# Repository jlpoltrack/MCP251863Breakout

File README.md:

# MCP251863Breakout

A CAN FD breakout: an MCP251863 (CAN FD controller with integrated transceiver) on SPI, with an
onboard 3.3 V regulator and 120 Ω termination. All connections are solder pads.

Designed in KiCad 10. See [SimpleCANBreakout](https://github.com/jlpoltrack/SimpleCANBreakout) for a classic-CAN
transceiver-only board.

## Features

- MCP251863 CAN FD controller + transceiver (SSOP-28), SPI interface, STBY on its own pad
- 4-pin crystal (Y1, 2016) for the controller clock
- AMS1117 3.3 V LDO for VDD/VIO; transceiver VCC from +5V
- 120 Ω termination resistor, always fitted
- Parts on the top side only

## Connections

All pads are 2.0 × 2.0 mm, labelled with their signal name.

| Pad  | Signal                              |
|------|-------------------------------------|
| CS   | SPI chip select (active low)        |
| SCK  | SPI clock                           |
| MOSI | SPI data in (SDI)                   |
| MISO | SPI data out (SDO)                  |
| INT  | interrupt (active low)              |
| INT0 | GPIO0 / TX interrupt (active low)   |
| INT1 | GPIO1 / RX interrupt (active low)   |
| CLKO | clock output                        |
| STBY | transceiver standby (high = standby) |
| CANH | CAN bus high                        |
| CANL | CAN bus low                         |
| PWR  | +5V (two pads: bottom edge, and beside CANH) |
| GND  | GND (two pads: bottom edge, and beside CANL) |

SPI, interrupt and STBY pins are 3.3 V logic (VIO = 3.3 V). STBY has no pull-down on the board: drive it low (or tie it
to GND) for normal operation; the transceiver goes to standby when it is high. INT0 (GPIO0) can drive it as XSTBY.

## Termination

R1 (120 Ω) is permanently connected across CANH/CANL, so the board is meant to sit at an end of the bus. Leave R1
unpopulated if the board is used mid-bus.

## Bill of materials

| Ref                  | Value           | Package    | LCSC    |
|----------------------|-----------------|------------|---------|
| U1                   | MCP251863T-H/SS | SSOP-28    |         |
| U2                   | AMS1117-3.3     | SOT-223    | C6186   |
| Y1                   | crystal         | 2016 4-pin |         |
| C1, C4, C10, C12     | 10 µF 25 V X5R  | 0603       | C96446  |
| C2, C3, C5, C6, C7   | 100 nF 50 V X7R | 0603       | C14663  |
| C8, C9               | 10 pF 50 V C0G  | 0603       | C1634   |
| R1                   | 120 Ω 1 %       | 0603       | C22787  |

All LCSC numbers above are JLC basic parts. U1 and Y1 have none set.

## Files

- `MCP251863Breakout.kicad_sch` / `.kicad_pcb` / `.kicad_pro` — KiCad project
- `MCP251863Breakout.pdf` — schematic
- `production/` — fabrication outputs generated with the [Fabrication Toolkit](https://github.com/bennymeg/Fabrication-Toolkit) plugin: Gerbers and drill files (`MCP251863Breakout.zip`), BOM, and pick-and-place positions, ready for JLCPCB

## License

[MIT](LICENSE)

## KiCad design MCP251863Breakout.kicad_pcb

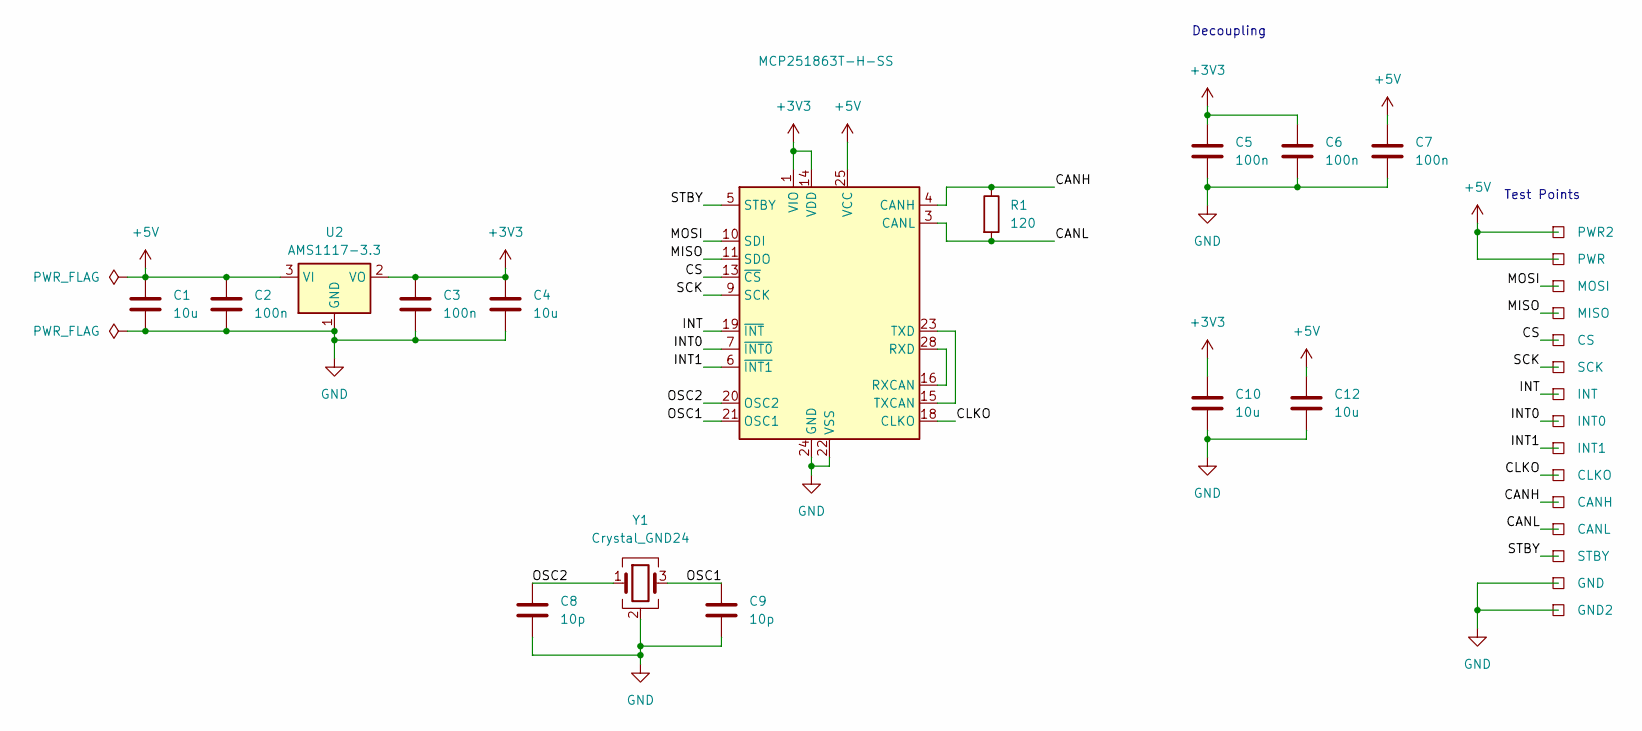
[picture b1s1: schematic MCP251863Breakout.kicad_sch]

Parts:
C1, C4, C10, C12: 10u; C_0603_1608Metric_Pad1.08x0.95mm_HandSolder; LCSC Part C96446
C2, C3, C5, C6, C7: 100n; C_0603_1608Metric_Pad1.08x0.95mm_HandSolder; LCSC Part C14663
C8, C9: 10p; C_0603_1608Metric_Pad1.08x0.95mm_HandSolder; LCSC Part C1634
CANH: TestPoint_Square; TestPoint_Pad_2.0x2.0mm
CANL: TestPoint_Square; TestPoint_Pad_2.0x2.0mm
CLKO: TestPoint_Square; TestPoint_Pad_2.0x2.0mm
CS: TestPoint_Square; TestPoint_Pad_2.0x2.0mm
GND, GND2: TestPoint_Square; TestPoint_Pad_2.0x2.0mm
INT, INT0, INT1: TestPoint_Square; TestPoint_Pad_2.0x2.0mm
MISO: TestPoint_Square; TestPoint_Pad_2.0x2.0mm
MOSI: TestPoint_Square; TestPoint_Pad_2.0x2.0mm
PWR, PWR2: TestPoint_Square; TestPoint_Pad_2.0x2.0mm
R1: 120; C_0603_1608Metric_Pad1.08x0.95mm_HandSolder; LCSC Part C22787
SCK: TestPoint_Square; TestPoint_Pad_2.0x2.0mm
STBY: TestPoint_Square; TestPoint_Pad_2.0x2.0mm
U1: MCP251863T-H-SS; SSOP-28_5.3x10.2mm_P0.65mm
U2: AMS1117-3.3; SOT-223-3_TabPin2; LCSC Part C6186
Y1: Crystal_GND24; Crystal_SMD_2016-4Pin_2.0x1.6mm

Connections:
+3V3: C3.1, C4.1, C5.1, C6.1, C10.1, U1.1 (VIO), U1.14 (VDD), U2.2 (VO)
+5V: C1.1, C2.1, C7.1, C12.1, PWR.1 (1_1), PWR2.1 (1_1), U1.25 (VCC), U2.3 (VI)
/CANH: CANH.1 (1_1), R1.1, U1.4 (CANH)
/CANL: CANL.1 (1_1), R1.2, U1.3 (CANL)
/CLKO: CLKO.1 (1_1), U1.18 (CLKO)
/CS: CS.1 (1_1), U1.13 (~CS)
/INT: INT.1 (1_1), U1.19 (~INT)
/INT0: INT0.1 (1_1), U1.7 (~INT0)
/INT1: INT1.1 (1_1), U1.6 (~INT1)
/MISO: MISO.1 (1_1), U1.11 (SDO)
/MOSI: MOSI.1 (1_1), U1.10 (SDI)
/OSC1: C9.1, U1.21 (OSC1), Y1.3
/OSC2: C8.1, U1.20 (OSC2), Y1.1
/SCK: SCK.1 (1_1), U1.9 (SCK)
/STBY: STBY.1 (1_1), U1.5 (STBY)
GND: C1.2, C2.2, C3.2, C4.2, C5.2, C6.2, C7.2, C8.2, C9.2, C10.2, C12.2, GND.1 (1_1), GND2.1 (1_1), U1.22 (VSS), U1.24 (GND), U2.1 (GND), Y1.2 (G), Y1.4 (G)
unnamed: U1.16 (RXCAN), U1.28 (RXD)
unnamed: U1.15 (TXCAN), U1.23 (TXD)

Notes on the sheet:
Decoupling
Test Points

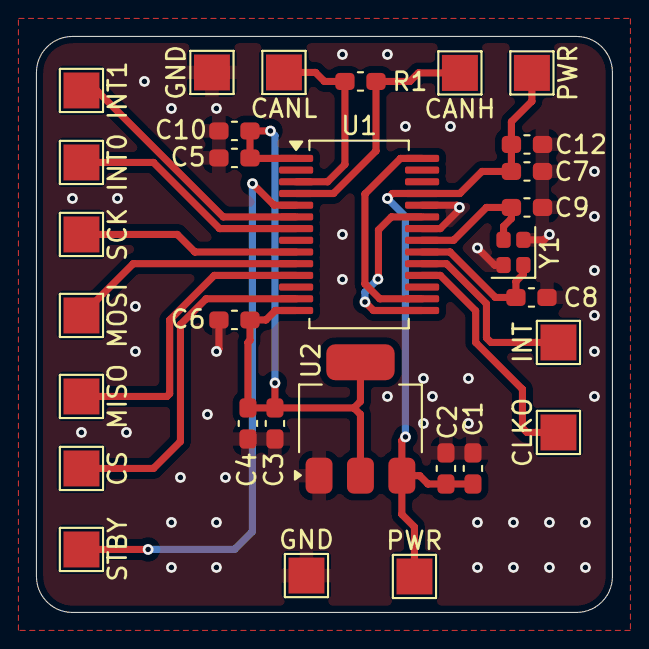
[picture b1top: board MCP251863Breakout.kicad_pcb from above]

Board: 2 copper layers, 32.0 x 32.0 mm, 30 parts (0 on the bottom side), 18 nets.

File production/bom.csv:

Designator,Footprint,Quantity,Value,LCSC Part #
"C1, C10, C12, C4",0603,4,10u,C96446
"C2, C3, C5, C6, C7",0603,5,100n,C14663
"C8, C9",0603,2,10p,C1634
"CANH, CANL, CLKO, CS, GND, GND2, INT, INT0, INT1, MISO, MOSI, PWR, PWR2, SCK, STBY",TestPoint_Pad_2.0x2.0mm,15,TestPoint_Square,
R1,0603,1,120,C22787
U1,SSOP-28_5.3x10.2mm_P0.65mm,1,MCP251863T-H-SS,
U2,SOT-223-3_TabPin2,1,AMS1117-3.3,C6186
Y1,Crystal_SMD_2016-4Pin_2.0x1.6mm,1,Crystal_GND24,
